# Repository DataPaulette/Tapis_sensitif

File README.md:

# /Tapis_sensitif/
 - Date : 13/08/2015
 - Project : http://datapaulette.org/Tapis_sensitif/
 - Repository : https://github.com/DataPaulette/Tapis_sensitif/
 
This project is under construction, all codes are work in progress. 

#/Tapis_sensitif/I2C_network_processing/
This folder include à processing sketch allowing mapping to trigger MIDI notes.
The following contributed libraries are needed :
 - theMidiBus
 - controlP5
 - (Linux) To alow non-root users permission to use the Teensy device you will nead to install udev rule file : http://www.pjrc.com/teensy/td_download.html

#/Tapis_sensitif/I2C_matrix_MASTER/
https://www.arduino.cc/en/Main/Software
This folder include the Arduino code for the master device plugged on a computer via USB port.
You will also need to install the teensy plugin for Arduino :
https://www.pjrc.com/teensy/teensyduino.html

#/Tapis_sensitif/I2C_matrix_SLAVE/
This folder include the Arduino code for each sensitive slave device that communicate over a four wire I2C bus.
The following contributed libraries are needed :
 - elapsedMillis

#/Tapis_sensitif/Eagle_board/
This folder include the Eagle source code of the electronic board made for the project.
http://www.cadsoftusa.com/download-eagle/
The file 7_BIT_ARRAY_COUNT.csv is useful to configure the dip switch of each board.
This 7 bit dip switch is used to configure the address of each board.

#Confugure the Midi server
 - Linux START virtal midi : modprobe snd-virmidi 
  - use QjackCtl to do the midi routing
 - MacOs ??
 - Windows ??

#TODO
 - ix the LOAD end SAVE fonction under MacOs
 - RPC library for arduino !?
 - The DIP switch on the PCB can be replace with a simple solderable traces.
 - Add optimized link state routing protocol :
  - https://fr.wikipedia.org/wiki/Optimized_link_state_routing_protocol
  - http://tools.ietf.org/html/rfc3626
  - https://github.com/moussu/GLiP/tree/master/source/Source

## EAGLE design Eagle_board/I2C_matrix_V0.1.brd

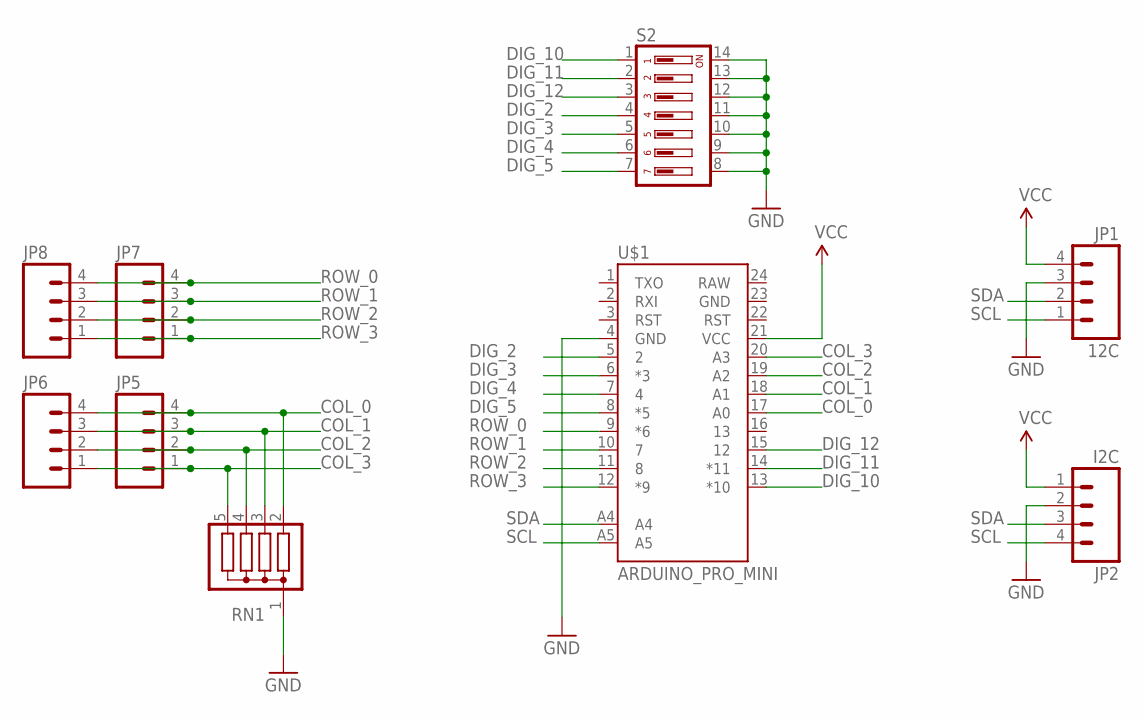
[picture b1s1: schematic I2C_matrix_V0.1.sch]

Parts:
JP1: 12C; 1X04-SMD_LONG
JP2: I2C; 1X04-SMD_LONG
JP5, JP6, JP7, JP8: M04LONGPADS; 1X04_LONGPADS
RN1: G04R; SIL5
S2: DIP07YL
U$1: ARDUINO_PRO_MINI

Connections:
COL_0: JP5.4, JP6.4, RN1.2, U$1.17 (A0)
COL_1: JP5.3, JP6.3, RN1.3, U$1.18 (A1)
COL_2: JP5.2, JP6.2, RN1.4, U$1.19 (A2)
COL_3: JP5.1, JP6.1, RN1.5, U$1.20 (A3)
DIG_2: S2.4, U$1.5 (2)
DIG_3: S2.5, U$1.6 (*3)
DIG_4: S2.6, U$1.7 (4)
DIG_5: S2.7, U$1.8 (*5)
DIG_10: S2.1, U$1.13 (*10)
DIG_11: S2.2, U$1.14 (*11)
DIG_12: S2.3, U$1.15 (12)
GND: JP1.3, JP2.2, RN1.1, S2.8, S2.9, S2.10, S2.11, S2.12, S2.13, S2.14, U$1.4 (GND)
ROW_0: JP7.4, JP8.4, U$1.9 (*6)
ROW_1: JP7.3, JP8.3, U$1.10 (7)
ROW_2: JP7.2, JP8.2, U$1.11 (8)
ROW_3: JP7.1, JP8.1, U$1.12 (*9)
SCL: JP1.1, JP2.4, U$1.A5
SDA: JP1.2, JP2.3, U$1.A4
VCC: JP1.4, JP2.1, U$1.21 (VCC)

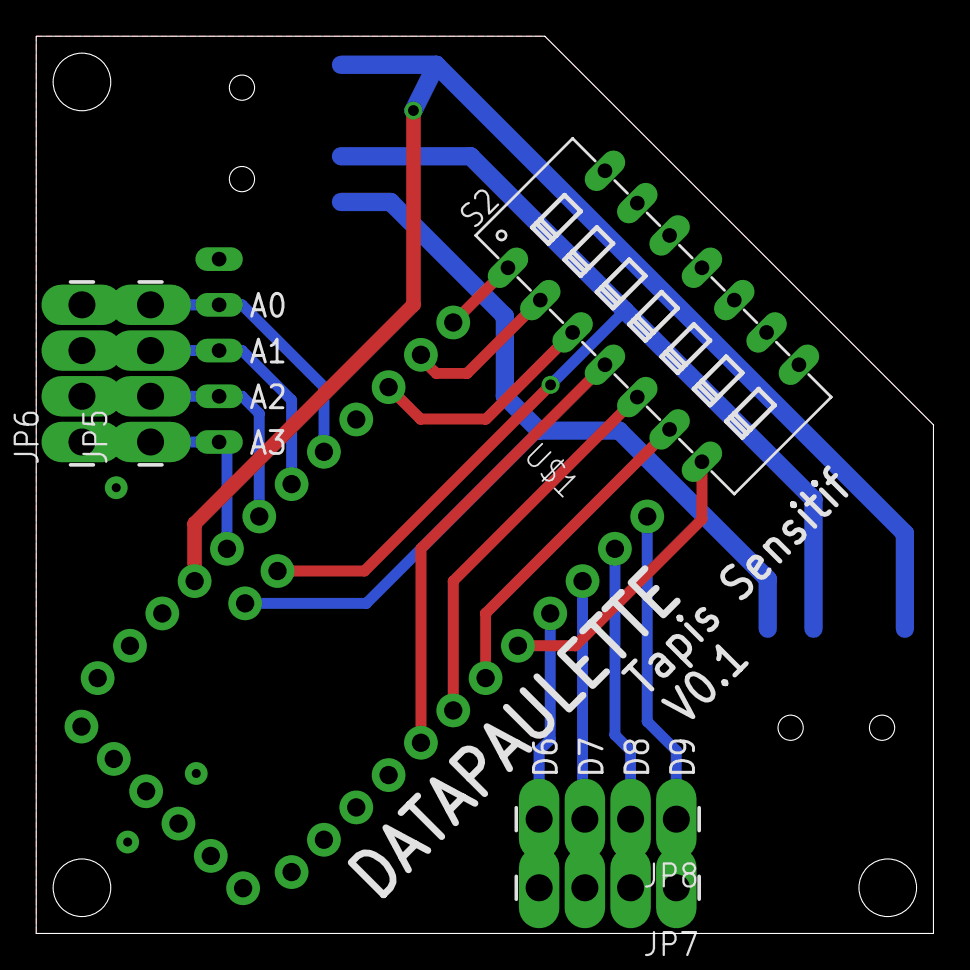
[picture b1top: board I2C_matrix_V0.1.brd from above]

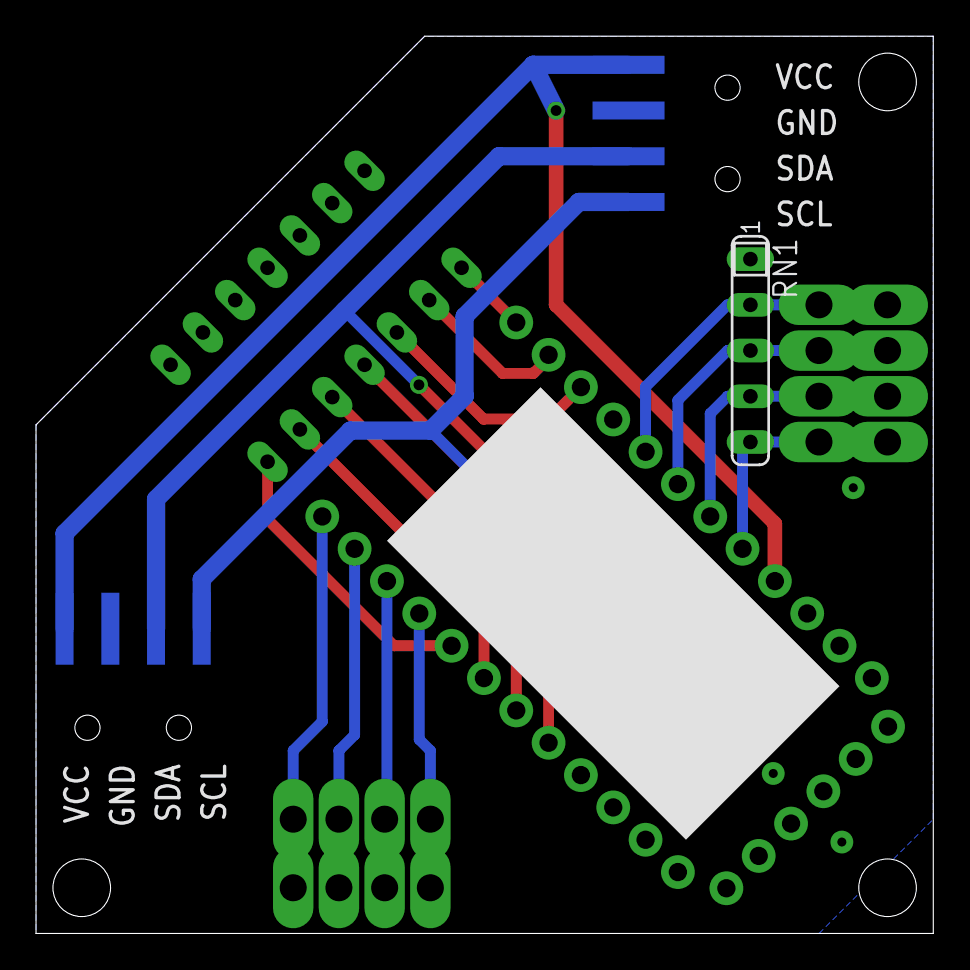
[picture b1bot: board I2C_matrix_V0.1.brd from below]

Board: 2 copper layers, 49.8 x 49.8 mm, 9 parts (3 on the bottom side), 19 nets.

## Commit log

2015-08-12 added MASTER file
2015-08-12 added SLAVE file
2015-08-12 added PROCESSING file
2015-08-12 test_01
2015-08-13 added REDME info
2015-08-13 added i2C master
2015-08-13 added I2C slave
2015-08-13 added processing mapping soft
2015-08-13 clean some files
2015-08-13 Updated for processing 3.x
2015-08-13 added eagle board
2015-08-13 added LICENSE
2015-08-13 added Arduino code for onboard Dill Switch
2015-08-13 added setNodeId fonction
2015-08-13 added 7-BIT array count
2015-08-15 Processing 3 compatibility
2015-08-15 Renamed files
2015-08-15 adding MIDI support
2015-08-16 Clean up
2015-08-29 Improved midibus
2015-09-28 add GERBER files
2015-10-10 fix midi output
2015-10-11 added Processing 3 support, improved midi OUT
2015-10-11 BUG FIX
2015-10-12 Cleaning
2015-10-26 added libraries
2015-10-27 added elapsedMillis lib
2015-10-27 moved libraries in to Processing folder
2015-10-27 added commants
2015-11-17 Update for the presentation
2016-01-19 last update
2016-03-04 changed DropdownList to ScrollableList
2016-03-04 Added udev tips

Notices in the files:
parts and their libraries:
SparkFun-Boards: Licensing: Creative Commons ShareAlike 4.0 International - https://creativecommons.org/licenses/by-sa/4.0
